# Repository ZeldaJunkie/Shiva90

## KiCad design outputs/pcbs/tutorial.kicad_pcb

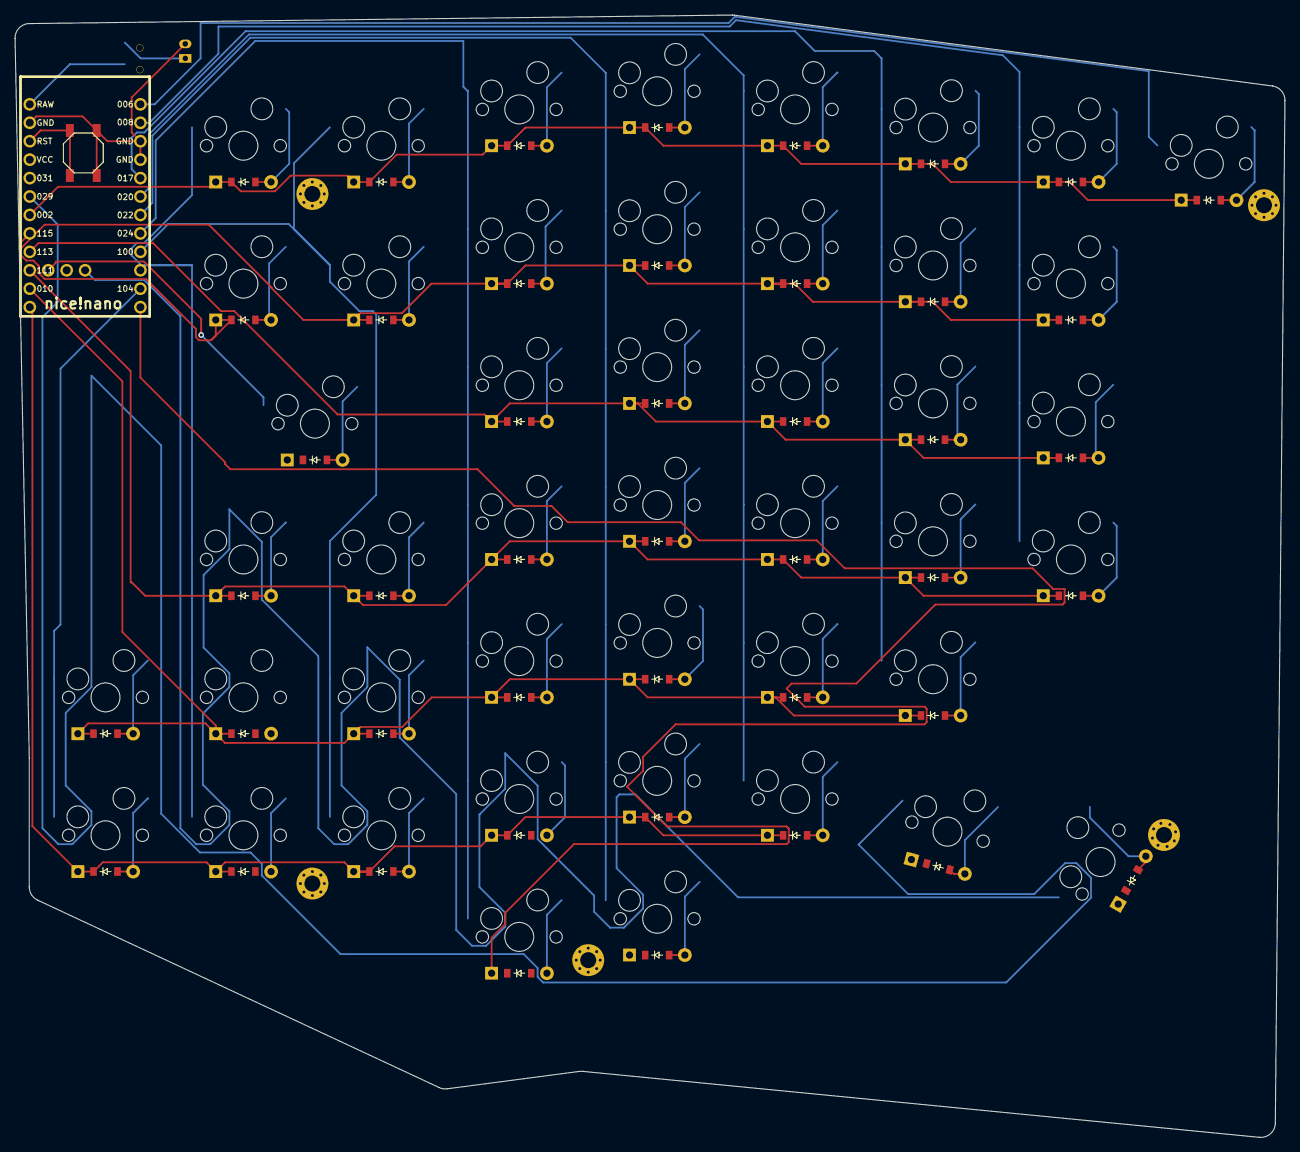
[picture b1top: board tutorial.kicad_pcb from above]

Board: 2 copper layers, 174.9 x 154.6 mm, 99 parts (0 on the bottom side), 68 nets.

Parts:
B1: SW_TACT_ALPS_SKQGABE010
D1, D2, D3, D4, D5, D6, D7, D8, D9, D10, D11, D12, D13, D14, D15, D16, D17, D18, D19, D20, D21, D22, D23, D24, D25, D26, D27, D28, D29, D30, D31, D32, D33, D34, D35, D36, D37, D38, D39, D40, D41, D42, D43, D44, D45: ComboDiode
JST1: JST_PH_S2B-PH-K_02x2.00mm_Angled
MCU1: nice_nano
S1, S2, S3, S4, S5, S6, S7, S8, S9, S10, S11, S12, S13, S14, S15, S16, S17, S18, S19, S20, S21, S22, S23, S24, S25, S26, S27, S28, S29, S30, S31, S32, S33, S34, S35, S36, S37, S38, S39, S40, S41, S42, S43, S44, S45: MX
T1: SPDT_C128955
_1, _2, _3, _4, _5: MountingHole_2.2mm_M2_Pad_Via

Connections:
GND: B1.1, JST1.2, MCU1.3, MCU1.4, MCU1.23
P002: D7.1, D12.1, D19.1, D26.1, D32.1, D37.1, D41.1, D42.1, MCU1.18
P006: MCU1.1, S42.1
P008: MCU1.2, S38.1, S39.1, S40.1, S41.1
P009: D1.1, D3.1, D8.1, D14.1, D21.1, D27.1, MCU1.13
P010: D2.1, D4.1, D9.1, D15.1, D22.1, D28.1, D33.1, MCU1.14
P011: MCU1.10, S3.1, S4.1, S5.1, S6.1, S7.1
P017: MCU1.5, S33.1, S34.1, S35.1, S36.1, S37.1
P020: MCU1.6, S27.1, S28.1, S29.1, S30.1, S31.1, S32.1
P022: MCU1.7, S20.1, S21.1, S22.1, S23.1, S24.1, S25.1, S26.1
P024: MCU1.8, S13.1, S14.1, S15.1, S16.1, S17.1, S18.1, S19.1
P029: MCU1.19, S43.1
P100: MCU1.9, S8.1, S9.1, S10.1, S11.1, S12.1
P101: MCU1.31, S45.1
P104: MCU1.11, S1.1, S2.1
P106: D13.1, D20.1, MCU1.12
P107: MCU1.33, S44.1
P111: D5.1, D10.1, D16.1, D23.1, D29.1, D34.1, D38.1, MCU1.15
P113: D17.1, D24.1, D30.1, D35.1, D39.1, MCU1.16
P115: D6.1, D11.1, D18.1, D25.1, D31.1, D36.1, D40.1, MCU1.17
RAW: MCU1.24, T1.2
RST: B1.2, MCU1.22
arrows_bottom: D2.2, S2.2
arrows_mod: D1.2, S1.2
f6_fun: D42.2, S42.2
f45rfc_fun: D41.2, S41.2
f45rfc_home: D38.2, S38.2
f45rfc_num: D40.2, S40.2
f45rfc_top: D39.2, S39.2
index_bottom: D28.2, S28.2
index_fun: D32.2, S32.2
index_home: D29.2, S29.2
index_mod: D27.2, S27.2
index_num: D31.2, S31.2
index_top: D30.2, S30.2
inner_bottom: D33.2, S33.2
inner_fun: D37.2, S37.2
inner_home: D34.2, S34.2
inner_num: D36.2, S36.2
inner_top: D35.2, S35.2
layer_default: D43.2, S43.2
middle_bottom: D22.2, S22.2
middle_fa: D20.2, S20.2
middle_fun: D26.2, S26.2
middle_home: D23.2, S23.2
middle_mod: D21.2, S21.2
middle_num: D25.2, S25.2
middle_top: D24.2, S24.2
outer_bottom: D4.2, S4.2
outer_fun: D7.2, S7.2
outer_home: D5.2, S5.2
outer_mod: D3.2, S3.2
outer_num: D6.2, S6.2
pinky_bottom: D9.2, S9.2
pinky_fun: D12.2, S12.2
pinky_home: D10.2, S10.2
pinky_mod: D8.2, S8.2
pinky_num: D11.2, S11.2
pos: JST1.1, T1.1
ring_bottom: D15.2, S15.2
ring_fa: D13.2, S13.2
ring_fun: D19.2, S19.2
ring_home: D16.2, S16.2
ring_mod: D14.2, S14.2
ring_num: D18.2, S18.2
ring_top: D17.2, S17.2
space_default: D44.2, S44.2
tab_default: D45.2, S45.2

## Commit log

2024-12-23 Rename _autosave-tutorial.kicad_pcb to outputs/pcbs/_autosave-tutorial.kicad_pcb
2024-12-23 Rename board.dxf to outputs/outlines/board.dxf
2024-12-23 Rename combo.dxf to outlines/combo.dxf
2024-12-23 Rename outlines/combo.dxf to outputs/outlines/combo.dxf
2024-12-23 Rename keys.dxf to outputs/outlines/keys.dxf
2024-12-23 Rename mounting.dxf to outputs/outlines/mounting.dxf
2024-12-23 Rename mountinghole.js to footprints/mountinghole.js
2024-12-23 Rename nice_nano.js to footprints/nice_nano.js
2024-12-23 Rename raw.dxf to outputs/outlines/raw.dxf
2024-12-23 Rename standoff.dxf to outputs/outlines/standoff.dxf
2024-12-23 Rename xlBoard.dxf to outputs/outlines/xlBoard.dxf
2024-12-23 Rename tutorial.kicad_pcb to outputs/pcbs/tutorial.kicad_pcb
2024-12-23 Rename tutorial.kicad_prl to outputs/pcbs/tutorial.kicad_prl
2024-12-23 Rename tutorial.kicad_pro to outputs/pcbs/tutorial.kicad_pro
